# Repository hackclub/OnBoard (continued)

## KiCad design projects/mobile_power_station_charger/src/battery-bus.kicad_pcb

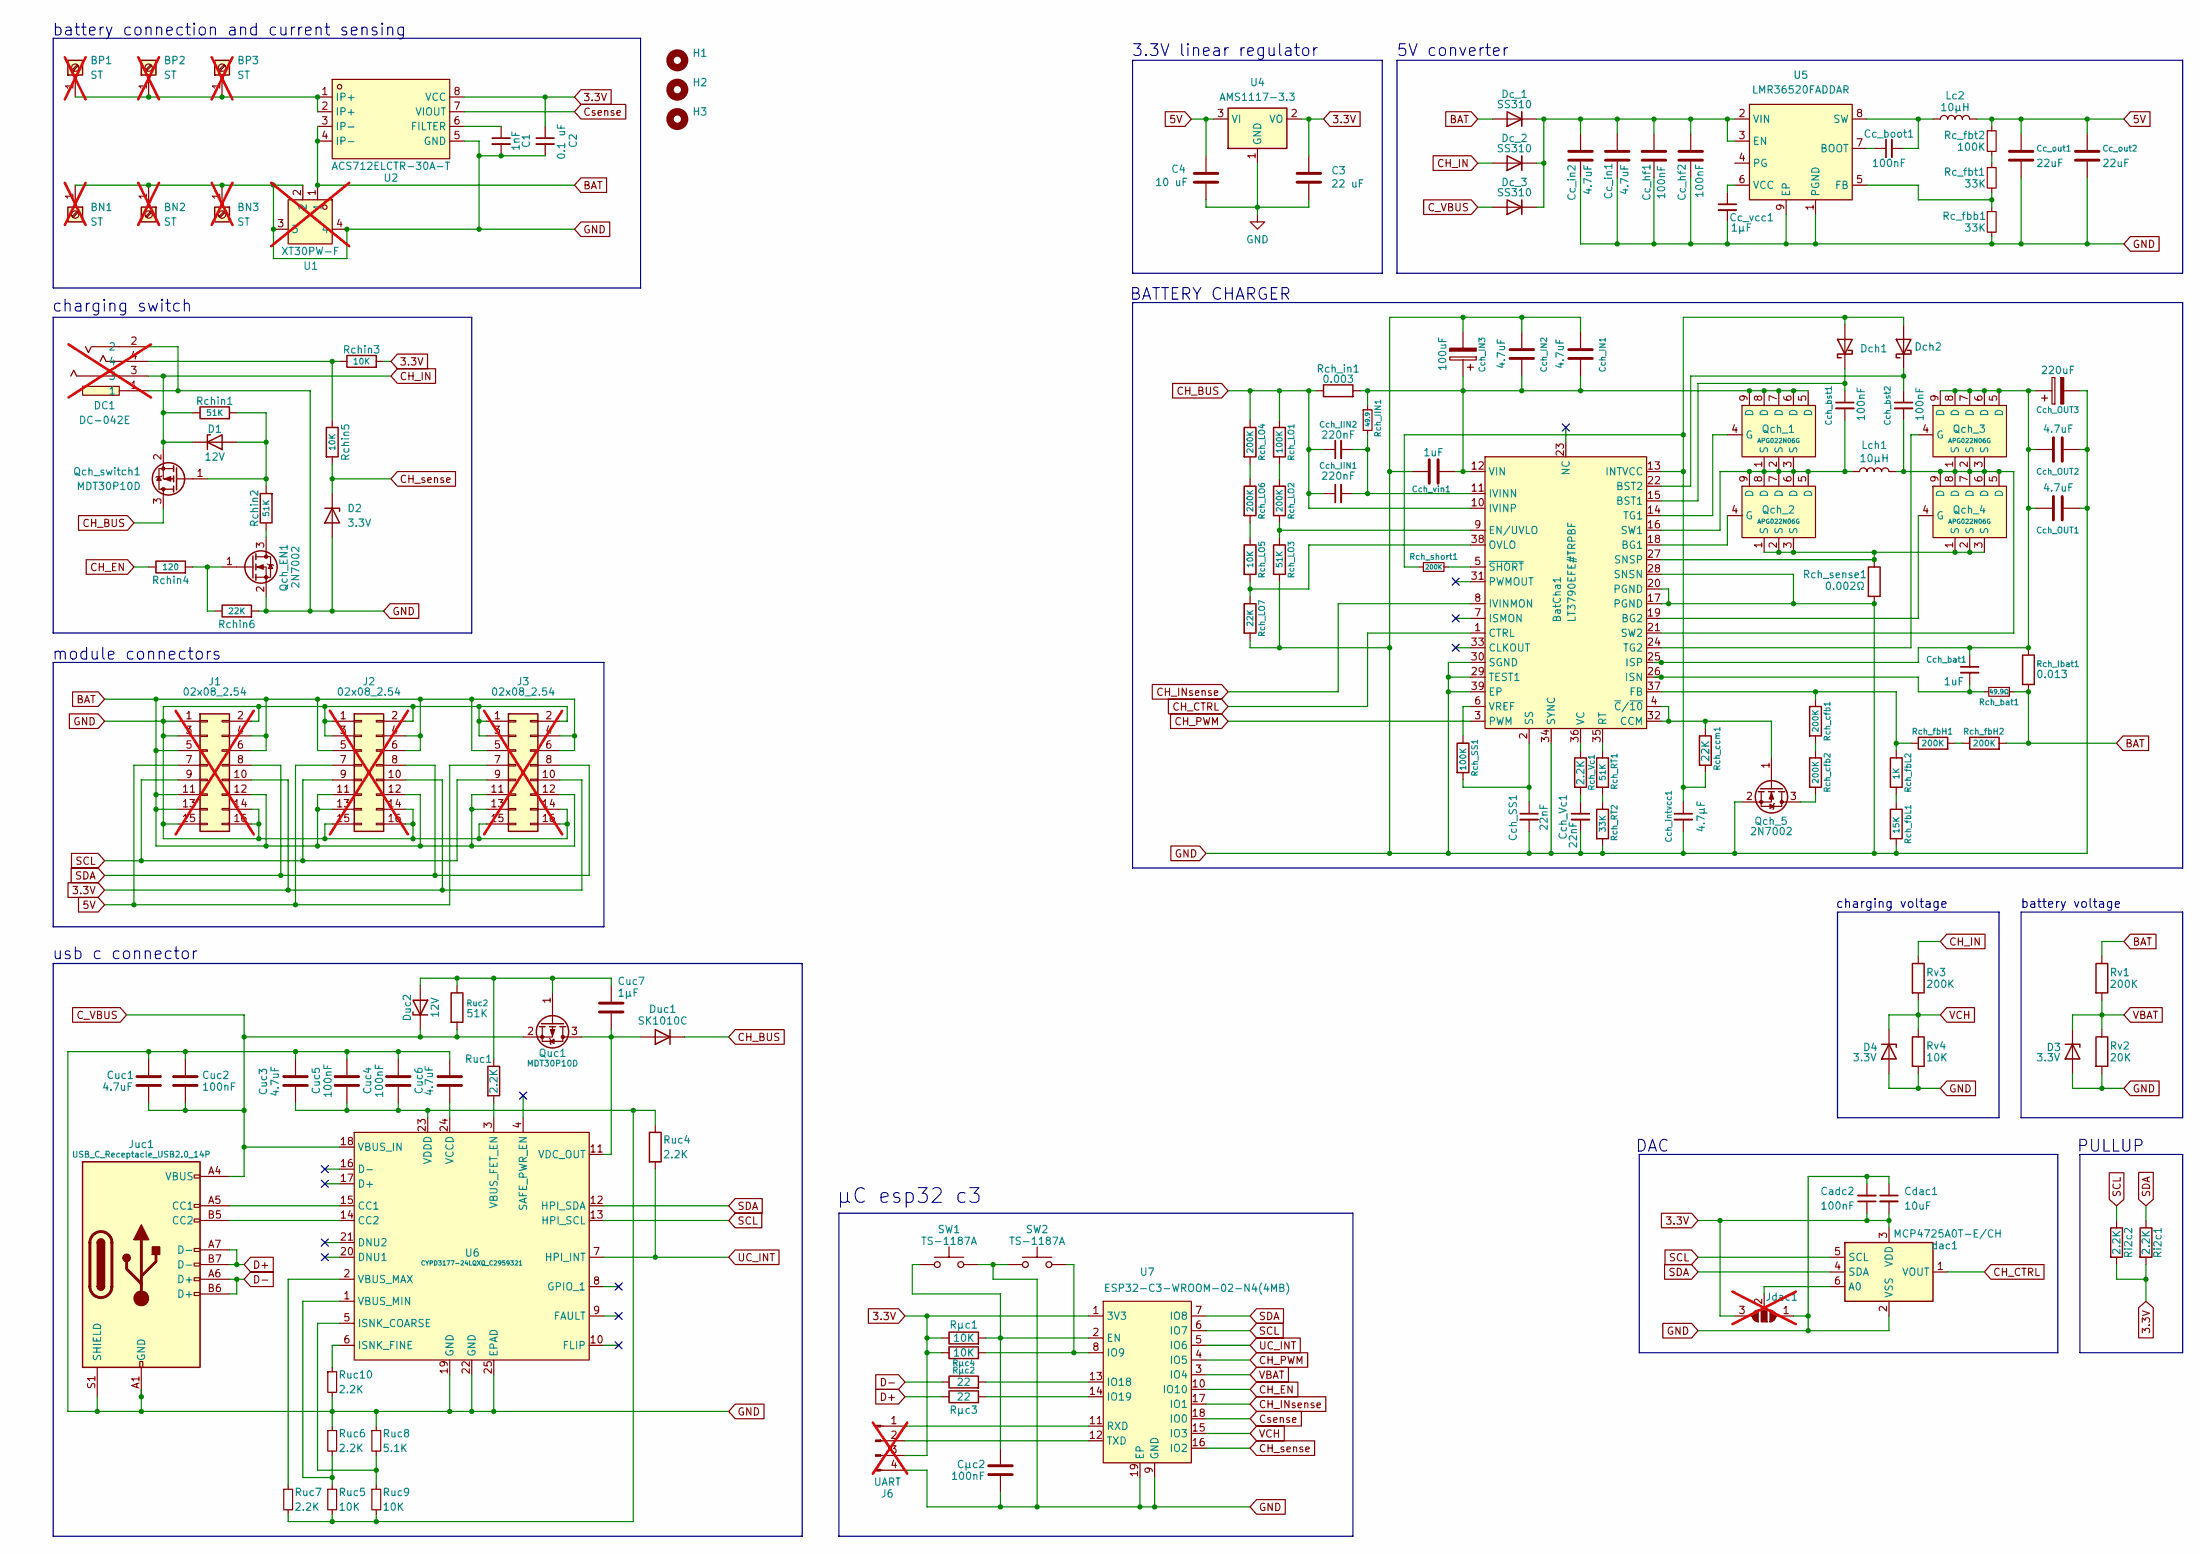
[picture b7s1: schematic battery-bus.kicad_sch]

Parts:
BN1, BN2, BN3: ST; connector; not fitted
BP1, BP2, BP3: ST; connector; not fitted
BatCha1: LT3790EFE#TRPBF; TSSOP-38_L9.8-W4.4-P0.50-LS6.4-BL-EP; LCSC Part C671549
C1: 1nF; C_0402_1005Metric
C2: 0.1 uF; C_0402_1005Metric
C3: 22 uF; C_0603_1608Metric
C4: 10 uF; C_0402_1005Metric
Cadc2: 100nF; C_0402_1005Metric
Cc_boot1: 100nF; C_0402_1005Metric
Cc_hf1, Cc_hf2: 100nF; C_0805_2012Metric
Cc_in1, Cc_in2: 4.7uF; C_1210_3225Metric
Cc_out1, Cc_out2: 22uF; C_0603_1608Metric
Cc_vcc1: 1μF; C_0402_1005Metric
Cch_IIN1, Cch_IIN2: 220nF; C_0402_1005Metric
Cch_IN1, Cch_IN2: 4.7uF; C_1210_3225Metric
Cch_IN3: 100uF; CP_Elec_10x10
Cch_OUT1, Cch_OUT2: 4.7uF; C_0805_2012Metric
Cch_OUT3: 220uF; CP_Elec_10x10
Cch_SS1: 22nF; C_0603_1608Metric
Cch_Vc1: 22nF; C_0603_1608Metric
Cch_bat1: 1uF; C_0402_1005Metric
Cch_bst1, Cch_bst2: 100nF; C_0402_1005Metric
Cch_intvcc1: 4.7μF; C_0805_2012Metric
Cch_vin1: 1uF; C_1206_3216Metric
Cdac1: 10uF; C_0402_1005Metric
Cuc1, Cuc3, Cuc6: 4.7uF; C_0805_2012Metric
Cuc2, Cuc4, Cuc5: 100nF; C_0402_1005Metric
Cuc7: 1μF; C_0402_1005Metric
Cμc2: 100nF; C_0402_1005Metric
D1: 12V; D_SOD-123
D2, D3, D4: 3.3V; D_SOD-523
DC1: DC-042E; DC-IN-TH_DC-042E; LCSC Part C397340; not fitted
Dc_1, Dc_2, Dc_3: SS310; D_SMA
Dch1, Dch2: D_Schottky; D_SOD-323F
Duc1: SK1010C; D_SMC
Duc2: 12V; D_SOD-123
H1, H2, H3: MountingHole; MountingHole_1.152mm
J1, J2, J3: 02x08_2.54; PinSocket_2x08_P2.54mm_Vertical_SMD; not fitted
J6: UART; PinHeader_1x04_P1.27mm_Vertical; not fitted
Jdac1: SolderJumper_3_Open; SolderJumper-3_P1.3mm_Open_Pad1.0x1.5mm_NumberLabels; not fitted
Juc1: USB_C_Receptacle_USB2.0_14P; TYPE-C-SMD_MC-108-DG16
Lc2: 10μH; IND-SMD_L7.3-W6.6
Lch1: 10μH; IND-SMD_L17.5-W17.0_YXMAC1770
Qch_1, Qch_2, Qch_3, Qch_4: APG022N06G; PDFN-8_L5.8-W4.9-P1.27-LS6.1-BL; LCSC Part C2995347
Qch_5: 2N7002; SOT-23
Qch_EN1: 2N7002; SOT-23
Qch_switch1: MDT30P10D; TO-252-2
Quc1: MDT30P10D; TO-252-2
Rc_fbb1: 33K; R_0402_1005Metric
Rc_fbt1: 33K; R_0402_1005Metric
Rc_fbt2: 100K; R_0402_1005Metric
Rch_IIN1: 49.9; R_0402_1005Metric
Rch_Ibat1: 0.013; R_2512_6332Metric; LCSC Part C2076271
Rch_LO1: 100K; R_0402_1005Metric
Rch_LO2, Rch_LO4, Rch_LO6: 200K; R_0402_1005Metric
Rch_LO3: 51K; R_0402_1005Metric
Rch_LO5: 10K; R_0402_1005Metric
Rch_LO7: 22K; R_0402_1005Metric
Rch_RT1: 51K; R_0402_1005Metric
Rch_RT2: 33K; R_0402_1005Metric
Rch_SS1: 100K; R_0402_1005Metric
Rch_Vc1: 2.2K; R_0402_1005Metric
Rch_bat1: 49.9Ω; R_0402_1005Metric
Rch_ccm1: 22K; R_0402_1005Metric
Rch_cfb1, Rch_cfb2: 200K; R_0402_1005Metric
Rch_fbH1, Rch_fbH2: 200K; R_0402_1005Metric
Rch_fbL1: 15K; R_0402_1005Metric
Rch_fbL2: 1K; R_0402_1005Metric
Rch_in1: 0.003; R_2512_6332Metric; LCSC Part C2874148
Rch_sense1: 0.002Ω; R_2512_6332Metric; LCSC Part C349182
Rch_short1: 200K; R_0402_1005Metric
Rchin1, Rchin2: 51K; R_0402_1005Metric
Rchin3, Rchin5: 10K; R_0402_1005Metric
Rchin4: 120; R_0402_1005Metric
Rchin6: 22K; R_0402_1005Metric
Ri2c1, Ri2c2: 2.2K; C_0402_1005Metric
Ruc1, Ruc4, Ruc6, Ruc7, Ruc10: 2.2K; R_0402_1005Metric
Ruc2: 51K; R_0402_1005Metric
Ruc5, Ruc9: 10K; R_0402_1005Metric
Ruc8: 5.1K; R_0402_1005Metric
Rv1, Rv3: 200K; C_0402_1005Metric
Rv2: 20K; C_0402_1005Metric
Rv4: 10K; C_0402_1005Metric
Rμc1, Rμc4: 10K; C_0402_1005Metric
Rμc2, Rμc3: 22; C_0402_1005Metric
SW1, SW2: TS-1187A; SW_Push_1P1T_XKB_TS-1187A
U1: XT30PW-F; CONN-TH_XT30PW-F-1; LCSC Part C2913282; not fitted
U2: ACS712ELCTR-30A-T; SOIC-8_L5.0-W4.0-P1.27-LS6.0-BL; LCSC Part C9932
U4: AMS1117-3.3; SOT-223-3_TabPin2; LCSC Part C6186
U5: LMR36520FADDAR; POWERPAD-SO-8_L4.9-W3.9-P1.27-LS6.0-BL-EP; LCSC Part C1858395
U6: CYPD3177-24LQXQ_C2959321; TQFN-24_L4.0-W4.0-P0.50-TL-EP2.8; LCSC Part C2959321
U7: ESP32-C3-WROOM-02-N4(4MB); BULETM-SMD_ESPRESSIF_ESP32-C3-WROOM-02-N4-4MB; LCSC Part C2934560
dac1: MCP4725A0T-E/CH; SOT-23-6

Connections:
3.3V: C2.1, C3.1, Cadc2.1, Cdac1.2, J1.10, J2.10, J3.10, J6.3, Jdac1.3 (B), Rchin3.2, Ri2c1.2, Ri2c2.2, Rμc1.1, Rμc4.1, U2.8 (VCC), U4.2 (VO), U7.1 (3V3), dac1.3 (VDD)
5V: C4.2, Cc_out1.1, Cc_out2.1, J1.7, J2.7, J3.7, Lc2.2, Rc_fbt2.1, U4.3 (VI)
BAT: Dc_1.2 (A), J1.4, J1.5, J1.6, J1.11, J1.12, J1.13, J2.4, J2.5, J2.6, J2.11, J2.12, J2.13, J3.4, J3.5, J3.6, J3.11, J3.12, J3.13, Rch_Ibat1.2, Rch_bat1.1, Rch_fbH2.2, Rv1.1, U1.1, U2.3 (IP-), U2.4 (IP-)
CH_BUS: BatCha1.10 (IVINP), Cch_IIN1.1, Cch_IIN2.1, Duc1.1 (K), Qch_switch1.3 (D), Rch_LO1.1, Rch_LO4.1, Rch_in1.1
CH_CTRL: BatCha1.1 (CTRL), dac1.1 (VOUT)
CH_EN: Rchin4.1, U7.10 (IO10)
CH_IN: D1.1 (K), DC1.3, Dc_2.2 (A), Qch_switch1.2 (S), Rchin1.1, Rv3.1
CH_INsense: BatCha1.8 (IVINMON), U7.17 (IO1)
CH_PWM: BatCha1.3 (PWM), U7.4 (IO5)
CH_sense: D2.1 (K), Rchin5.2, U7.16 (IO2)
C_VBUS: Cuc1.1, Cuc2.2, Dc_3.2 (A), Duc2.1 (K), Juc1.A4 (VBUS), Juc1.A9 (VBUS), Juc1.B4 (VBUS), Juc1.B9 (VBUS), Quc1.2 (S), Ruc2.2, U6.18 (VBUS_IN)
Csense: U2.7 (VIOUT), U7.18 (IO0)
D+: Juc1.A7 (D-), Juc1.B7 (D-), Rμc3.1
D-: Juc1.A6 (D+), Juc1.B6 (D+), Rμc2.1
GND: BN1.1, BN2.1, BN3.1, BatCha1.17 (PGND), BatCha1.20 (PGND), BatCha1.28 (SNSN), BatCha1.29 (TEST1), BatCha1.30 (SGND), BatCha1.34 (SYNC), BatCha1.39 (EP), C1.2, C2.2, C3.2, C4.1, Cadc2.2, Cc_hf1.1, Cc_hf2.1, Cc_in1.1, Cc_in2.1, Cc_out1.2, Cc_out2.2, Cc_vcc1.2, Cch_IN1.2, Cch_IN2.2, Cch_IN3.2, Cch_OUT1.2, Cch_OUT2.2, Cch_OUT3.2, Cch_SS1.2, Cch_Vc1.2, Cch_intvcc1.2, Cch_vin1.1, Cdac1.1, Cuc1.2, Cuc2.1, Cuc3.2, Cuc4.2, Cuc5.2, Cuc6.1, Cμc2.1, D2.2 (A), D3.2 (A), D4.2 (A), DC1.1, DC1.2, J1.1, J1.2, J1.3, J1.14, J1.15, J1.16, J2.1, J2.2, J2.3, J2.14, J2.15, J2.16, J3.1, J3.2, J3.3, J3.14, J3.15, J3.16, J6.4, Jdac1.1 (A), Juc1.A1 (GND), Juc1.A12 (GND), Juc1.B1 (GND), Juc1.B12 (GND), Juc1.S1 (SHIELD), Qch_5.2 (S), Qch_EN1.2 (S), Rc_fbb1.2, Rch_LO3.2, Rch_LO7.2, Rch_RT2.2, Rch_fbL1.2, Rch_sense1.2, Rchin6.2, Ruc6.1, Ruc8.1, Ruc10.2, Rv2.2, Rv4.2, SW1.2, SW2.1, U1.2, U1.3, U1.4, U2.5 (GND), U4.1 (GND), U5.1 (PGND), U5.9 (EP), U6.19 (GND), U6.22 (GND), U6.25 (EPAD), U7.9 (GND), U7.19 (EP), dac1.2 (VSS)
unnamed: BP1.1, BP2.1, BP3.1, U2.1 (IP+), U2.2 (IP+)
unnamed: BatCha1.18 (BG1), Qch_2.4 (G)
unnamed: BatCha1.19 (BG2), Qch_4.4 (G)
unnamed: BatCha1.15 (BST1), Cch_bst1.1, Dch1.1 (K)
unnamed: BatCha1.22 (BST2), Cch_bst2.1, Dch2.1 (K)
unnamed: BatCha1.4 (~C/~10), BatCha1.32 (CCM), Qch_5.1 (G), Rch_ccm1.1
unnamed: BatCha1.9 (EN/UVLO), Rch_LO2.2, Rch_LO3.1
unnamed: BatCha1.37 (FB), Rch_cfb1.1, Rch_fbH1.1, Rch_fbL2.1
unnamed: BatCha1.13 (INTVCC), Cch_intvcc1.1, Dch1.2 (A), Dch2.2 (A), Rch_ccm1.2, Rch_short1.1
unnamed: BatCha1.26 (ISN), Cch_bat1.2, Rch_bat1.2
unnamed: BatCha1.25 (ISP), Cch_OUT1.1, Cch_OUT2.1, Cch_OUT3.1, Cch_bat1.1, Qch_3.5 (D), Qch_3.6 (D), Qch_3.7 (D), Qch_3.8 (D), Qch_3.9 (D), Rch_Ibat1.1
unnamed: BatCha1.11 (IVINN), Cch_IIN1.2, Cch_IIN2.2, Rch_IIN1.2
unnamed: BatCha1.38 (OVLO), Rch_LO5.2, Rch_LO7.1
unnamed: BatCha1.35 (RT), Rch_RT1.1
unnamed: BatCha1.27 (SNSP), Qch_2.1 (S), Qch_2.2 (S), Qch_2.3 (S), Qch_4.1 (S), Qch_4.2 (S), Qch_4.3 (S), Rch_sense1.1
unnamed: BatCha1.2 (SS), Cch_SS1.1, Rch_SS1.2
unnamed: BatCha1.16 (SW1), Cch_bst1.2, Lch1.1, Qch_1.1 (S), Qch_1.2 (S), Qch_1.3 (S), Qch_2.5 (D), Qch_2.6 (D), Qch_2.7 (D), Qch_2.8 (D), Qch_2.9 (D)
unnamed: BatCha1.21 (SW2), Cch_bst2.2, Lch1.2, Qch_3.1 (S), Qch_3.2 (S), Qch_3.3 (S), Qch_4.5 (D), Qch_4.6 (D), Qch_4.7 (D), Qch_4.8 (D), Qch_4.9 (D)
unnamed: BatCha1.14 (TG1), Qch_1.4 (G)
unnamed: BatCha1.24 (TG2), Qch_3.4 (G)
unnamed: BatCha1.36 (VC), Rch_Vc1.1
unnamed: BatCha1.12 (VIN), Cch_IN1.1, Cch_IN2.1, Cch_IN3.1, Cch_vin1.2, Qch_1.5 (D), Qch_1.6 (D), Qch_1.7 (D), Qch_1.8 (D), Qch_1.9 (D), Rch_IIN1.1, Rch_in1.2
unnamed: BatCha1.6 (VREF), Rch_SS1.1
unnamed: BatCha1.5 (~SHORT), Rch_short1.2
unnamed: Cch_Vc1.1, Rch_Vc1.2
unnamed: D1.2 (A), Qch_switch1.1 (G), Rchin1.2, Rchin2.2
unnamed: DC1.4, Rchin3.1, Rchin5.1
unnamed: Cc_hf1.2, Cc_hf2.2, Cc_in1.2, Cc_in2.2, Dc_1.1 (K), Dc_2.1 (K), Dc_3.1 (K), U5.2 (VIN), U5.3 (EN)
unnamed: Cuc7.2, Duc1.2 (A), Quc1.3 (D), U6.11 (VDC_OUT)
unnamed: Cuc7.1, Duc2.2 (A), Quc1.1 (G), Ruc1.1, Ruc2.1
unnamed: J6.1, U7.11 (RXD)
unnamed: J6.2, U7.12 (TXD)
unnamed: Jdac1.2 (C), dac1.6 (A0)
unnamed: Juc1.A5 (CC1), U6.15 (CC1)
unnamed: Juc1.B5 (CC2), U6.14 (CC2)
unnamed: Qch_5.3 (D), Rch_cfb2.2
unnamed: Qch_EN1.3 (D), Rchin2.1
unnamed: Qch_EN1.1 (G), Rchin4.2, Rchin6.1
unnamed: Rc_fbt1.1, Rc_fbt2.2
unnamed: Rch_LO1.2, Rch_LO2.1
unnamed: Rch_LO4.2, Rch_LO6.1
unnamed: Rch_LO5.1, Rch_LO6.2
unnamed: Rch_RT1.2, Rch_RT2.1
unnamed: Rch_cfb1.2, Rch_cfb2.1
unnamed: Rch_fbH1.2, Rch_fbH2.1
unnamed: Rch_fbL1.1, Rch_fbL2.2
unnamed: C1.1, U2.6 (FILTER)
unnamed: Cc_boot1.1, U5.7 (BOOT)
unnamed: Rc_fbb1.1, Rc_fbt1.2, U5.5 (FB)
unnamed: Cc_boot1.2, Lc2.1, U5.8 (SW)
unnamed: Cc_vcc1.1, U5.6 (VCC)
unnamed: Ruc8.2, Ruc9.1, U6.5 (ISNK_COARSE)
unnamed: Ruc10.1, U6.6 (ISNK_FINE)
unnamed: Ruc1.2, U6.3 (VBUS_FET_EN)
unnamed: Ruc7.1, U6.2 (VBUS_MAX)
unnamed: Ruc5.1, Ruc6.2, U6.1 (VBUS_MIN)
unnamed: Cuc6.2, U6.24 (VCCD)
unnamed: Cuc3.1, Cuc4.1, Cuc5.1, Ruc4.1, Ruc5.2, Ruc7.2, Ruc9.2, U6.23 (VDDD)
unnamed: Cμc2.2, Rμc1.2, SW1.1, U7.2 (EN)
unnamed: Rμc4.2, SW2.2, U7.8 (IO9)
unnamed: Rμc2.2, U7.13 (IO18)
unnamed: Rμc3.2, U7.14 (IO19)
SCL: J1.9, J2.9, J3.9, Ri2c2.1, U6.13 (HPI_SCL), U7.6 (IO7), dac1.5 (SCL)
SDA: J1.8, J2.8, J3.8, Ri2c1.1, U6.12 (HPI_SDA), U7.7 (IO8), dac1.4 (SDA)
UC_INT: Ruc4.2, U6.7 (HPI_INT), U7.5 (IO6)
VBAT: D3.1 (K), Rv1.2, Rv2.1, U7.3 (IO4)
VCH: D4.1 (K), Rv3.2, Rv4.1, U7.15 (IO3)

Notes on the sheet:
usb c connector
BATTERY CHARGER
5V converter
battery voltage
charging switch
PULLUP
3.3V linear regulator
charging voltage
module connectors
battery connection and current sensing
μC esp32 c3
DAC

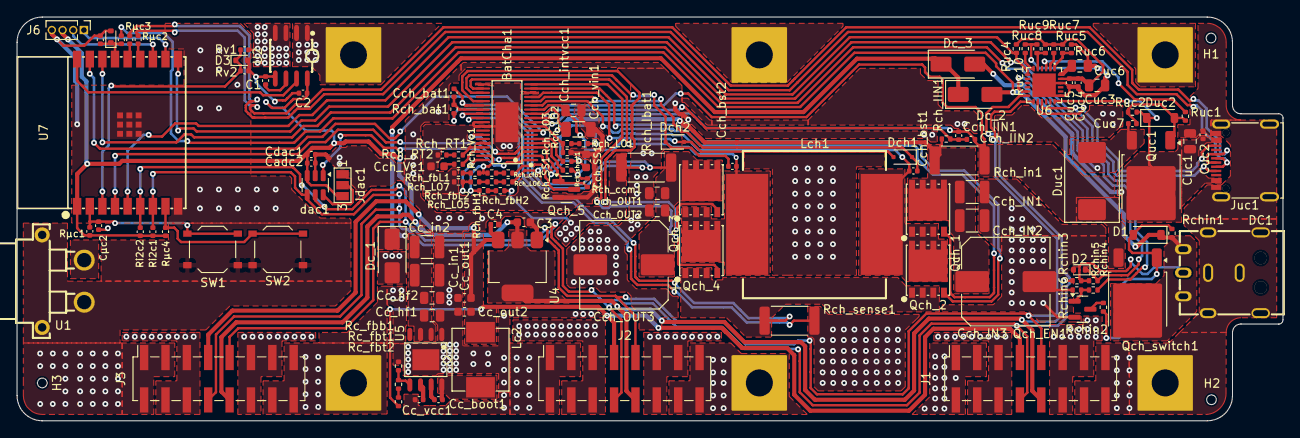
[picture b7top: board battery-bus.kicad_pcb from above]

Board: 2 copper layers, 150.5 x 48.0 mm, 136 parts (0 on the bottom side), 82 nets.

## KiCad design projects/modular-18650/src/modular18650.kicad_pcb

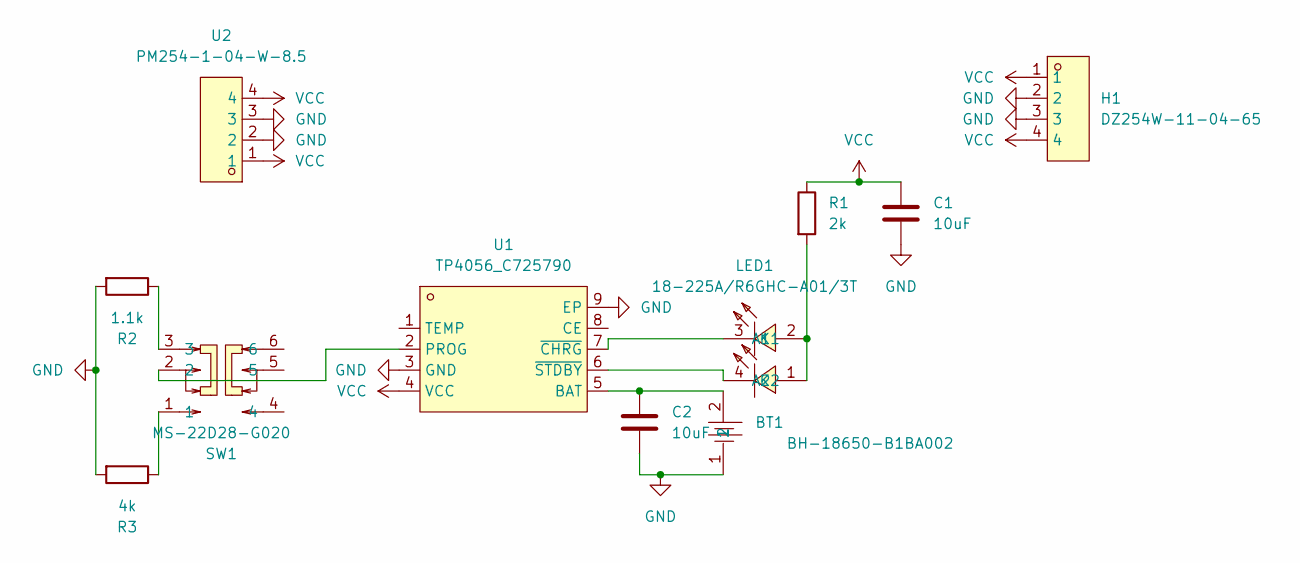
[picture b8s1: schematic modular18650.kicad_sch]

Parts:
BT1: BH-18650-B1BA002; BATTERY-SMD_18650-1S-L77.1-W20.7-1; LCSC Part C2988620
C1, C2: 10uF; C_0603_1608Metric; LCSC C1691
H1: DZ254W-11-04-65; HDR-TH_4P-P2.54-H-M-W10.3; LCSC Part C2935929
LED1: 18-225A/R6GHC-A01/3T; LED-SMD_4P-L1.6-W0.8-BR-RD; LCSC Part C264440
R1: 2k; R_0603_1608Metric; LCSC C22975
R2: 1.1k; R_0603_1608Metric; LCSC C22764
R3: 4k; R_0603_1608Metric; LCSC C2984443
SW1: MS-22D28-G020; SW-SMD_MS-22D28-G020; LCSC Part C963205
U1: TP4056_C725790; ESOP-8_L4.9-W3.9-P1.27-LS6.0-BL-EP; LCSC Part C725790
U2: PM254-1-04-W-8.5; HDR-TH_4P-P2.54-H-F-W10.0-N; LCSC Part C2897386

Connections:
GND: BT1.1, C1.2, C2.2, H1.2, H1.3, R2.2, R3.2, U1.3 (GND), U1.9 (EP), U2.2, U2.3
unnamed: LED1.1 (A2), LED1.2 (A1), R1.2
unnamed: LED1.3 (K1), U1.7 (~CHRG)
unnamed: LED1.4 (K2), U1.6 (~STDBY)
unnamed: R2.1, SW1.3
unnamed: R3.1, SW1.1
unnamed: BT1.2, C2.1, U1.5 (BAT)
unnamed: SW1.2, U1.2 (PROG)
VCC: C1.1, H1.1, H1.4, R1.1, U1.4 (VCC), U2.1, U2.4

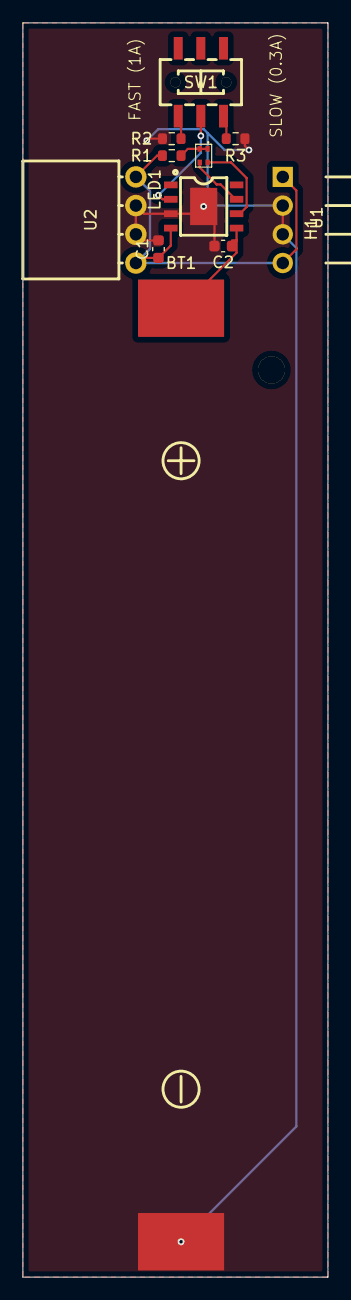
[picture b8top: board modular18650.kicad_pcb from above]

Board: 2 copper layers, 27.0 x 111.0 mm, 11 parts (0 on the bottom side), 9 nets.
